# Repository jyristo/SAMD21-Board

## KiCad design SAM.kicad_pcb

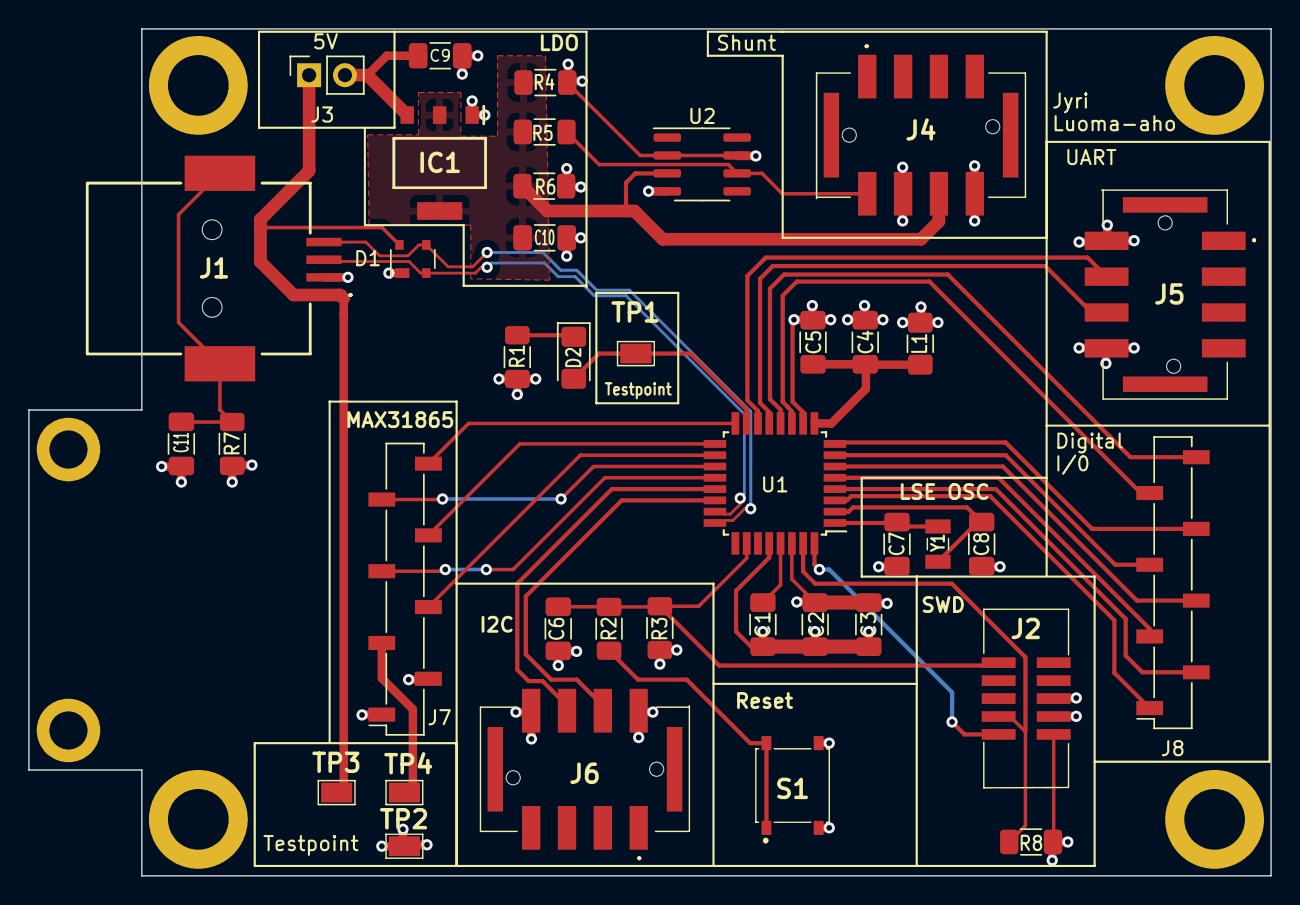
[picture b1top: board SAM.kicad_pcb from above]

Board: 4 copper layers, 88.0 x 60.0 mm, 45 parts (0 on the bottom side), 37 nets.

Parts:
C1, C6, C7, C8: 1uF; C_1206_3216Metric_Pad1.33x1.80mm_HandSolder
C2, C4, C9, C10: 10uF; C_1206_3216Metric_Pad1.33x1.80mm_HandSolder
C3, C5: 100nF; C_1206_3216Metric_Pad1.33x1.80mm_HandSolder
C11: 4.7nF; C_1206_3216Metric_Pad1.33x1.80mm_HandSolder
D1: PRTR5V0U2X; SOT-143
D2: LED; LED_1206_3216Metric_Pad1.42x1.75mm_HandSolder
H1, H2, H3, H4: M4 MountingHole; MountingHole_4.3mm_M4_ISO14580_Pad
H5, H6: M2.6 MountingHole; MountingHole_2.7mm_M2.5_ISO14580_Pad
IC1: NCV1117ST33T3G; SOT230P700X180-4N
J1: USB_B; KUSBXSMTBS1NB30
J2: 2002152100010E1LF
J3: SW_UIN; PinSocket_1x02_P2.54mm_Vertical
J4, J5, J6: 14010413101000
J7, J8: 2212SM-08G-75-B1-PCR; PinSocket_1x08_P2.54mm_Vertical_SMD_Pin1Right
L1: 30nH; L_1206_3216Metric_Pad1.42x1.75mm_HandSolder
R1: 820; R_1206_3216Metric_Pad1.30x1.75mm_HandSolder
R2: 330; R_1206_3216Metric_Pad1.30x1.75mm_HandSolder
R3: 2.2k; R_1206_3216Metric_Pad1.30x1.75mm_HandSolder
R4: 100m; R_1206_3216Metric_Pad1.30x1.75mm_HandSolder
R5: 100k; R_1206_3216Metric_Pad1.30x1.75mm_HandSolder
R6, R8: 1k; R_1206_3216Metric_Pad1.30x1.75mm_HandSolder
R7: 1M; R_1206_3216Metric_Pad1.30x1.75mm_HandSolder
S1: PTS526_SK15_SMTR2_LFS; PTS526SK15SMTR2LFS
TP1: LED; S275146R
TP2: GND; S275146R
TP3: VBUS; S275146R
TP4: 3.3V; S275146R
U1: ATSAMD21E18A-A; TQFP-32_7x7mm_P0.8mm
U2: MCP6L91RT-ESN; SOIC-8_3.9x4.9mm_P1.27mm
Y1: FC-135_32.7680KA-A5; FC135327680KAA5

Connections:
3V3_MAXOUT: J7.3, TP4.1
+3.3V: C2.2, C3.2, C6.2, J2.1 (VTref), J4.4, J5.2, J6.2, J7.1, L1.1, R3.2, R4.2, R8.1, U1.30 (VDDIN), U2.2 (-), U2.7 (V+)
+3.3VA: C4.2, C5.2, L1.2, U1.9 (VDDANA)
/LDO/SHUNT+: C10.1, IC1.2 (OUTPUT_1), IC1.4 (OUTPUT_2), J4.6, R4.1, R5.1, R6.2, U2.3 (+)
/LDO/SHUNTOUT: J4.2, R5.2, U2.6
/LDO/USB_VBUS: C9.1, IC1.3 (INPUT), J3.2
A0D14: J8.1, U1.3 (PA02)
A3D17: J8.3, U1.5 (PA04)
A4D18: J8.4, U1.6 (PA05)
AREF: J8.2, U1.4 (PA03)
D3: J8.8, U1.12 (PA09)
D4: J8.7, U1.11 (PA08)
D8: J8.5, U1.7 (PA06)
D9: J8.6, U1.8 (PA07)
DRDY: J7.8, U1.16 (PA15)
GND: C1.1, C2.1, C3.1, C4.1, C5.1, C7.1, C8.1, C9.2, C10.2, C11.2, D1.1 (GND), IC1.1 (GROUND), J1.4 (GND), J2.3 (GND), J2.5 (GND), J4.8, J5.8, J6.8, J7.2, R1.1, R6.1, R7.2, S1.3 (NO_1), S1.4 (NO_2), TP2.1, U1.10 (GND), U1.28 (GND), U2.4 (V-)
LED: D2.2 (A), TP1.1, U1.15 (PA14)
unnamed: D2.1 (K), R1.2
unnamed: R2.2, S1.1 (COM_1), S1.2 (COM_2)
unnamed: C1.2, U1.29 (VDDCORE)
RESET: C6.1, J2.10 (~RESET), R2.1, R3.1, U1.26 (~RESET)
SCL: J6.4, U1.22 (PA23)
SCLK: J7.4, U1.18 (PA17)
SDA: J6.6, U1.21 (PA22)
SDI: J7.6, U1.17 (PA16)
SDO: J7.5, U1.20 (PA19)
SHIELD: C11.1, J1.MP1, J1.MP2, R7.1
SWCLK: J2.4 (SWDCLK/TCK), R8.2, U1.31 (PA30)
SWDIO: J2.2 (SWDIO/TMS), U1.32 (PA31)
UART_RX: J5.4, U1.14 (PA11)
UART_TX: J5.6, U1.13 (PA10)
USB_D+: D1.3 (I/O2), J1.3 (D+), U1.24 (PA25)
USB_D-: D1.2 (I/O1), J1.2 (D-), U1.23 (PA24)
VBUS: D1.4 (VCC), J1.1 (VBUS), J3.1, TP3.1
XIN32: C7.2, U1.1 (PA00), Y1.1
XOUT32: C8.2, U1.2 (PA01), Y1.2
nCS: J7.7, U1.19 (PA18)

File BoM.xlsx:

Designator | Description | Footprint | Value | Manufacturer | Manufacturer Part Number | Vendor Link | Price | Quantity
Y1 | Crystals MINI SMD XTL 38.768 kHz | FC135327680KAA5 | FC-135_32.7680KA-A5 | Epson Timing | FC-135 32.7680KA-A5 | https://www.mouser.fi/ProductDetail/Epson-Timing/FC-135-32.7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 | 0.54 | 1
U2 | Instrumentation Amplifiers Sin, 500kHz, 800uA Gmin 1 v/v, I/O | SOIC-8_3.9x4.9mm_P1.27mm | MCP6L91RT-ESN | Microchip Technology | MCP6L91RT-ESN | https://www.mouser.fi/ProductDetail/Microchip-Technology/MCP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 | 1.58 | 1
U1 | ARM MCU 64KB 8KB32TQFP GRN 1.6-3.6V 48MHz | TQFP-32_7x7mm_P0.8mm | ATSAMD21E18A-AU | Microchip Technology | ATSAMD21E18A-AU | https://www.mouser.fi/ProductDetail/Microchip-Technology/ATS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 | 3.74 | 1
TP4 | Circuit Board Hardware - PCB SMT Mini Test Terminal, Reel | S275146R | 3.3V | Harwin | S2751-46R | https://www.mouser.fi/ProductDetail/Harwin/S2751-46R?qs=Daxo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 | 0.27900000000000003 | 1
TP3 | Circuit Board Hardware - PCB SMT Mini Test Terminal, Reel | S275146R | VBUS | Harwin | S2751-46R | https://www.mouser.fi/ProductDetail/Harwin/S2751-46R?qs=Daxo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 | 0.27900000000000003 | 1
TP2 | Circuit Board Hardware - PCB SMT Mini Test Terminal, Reel | S275146R | GND | Harwin | S2751-46R | https://www.mouser.fi/ProductDetail/Harwin/S2751-46R?qs=Daxo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 | 0.27900000000000003 | 1
TP1 | Circuit Board Hardware - PCB SMT Mini Test Terminal, Reel | S275146R | LED | Harwin | S2751-46R | https://www.mouser.fi/ProductDetail/Harwin/S2751-46R?qs=Daxo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 | 0.27900000000000003 | 1
S1 | Tactile Switches 50mA 12VDC | PTS526SK15SMTR2LFS | PTS526_SK15_SMTR2_LFS | C&K | PTS526_SK15_SMTR2_LFS | https://www.mouser.fi/ProductDetail/CK/PTS526-SK15-SMTR2-LFS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 | 0.108 | 1
R8,R6 | Thick Film Resistors - SMD 1K 1% | R_1206_3216Metric_Pad1.30x1.75mm_HandSolder | 1k | Bourns | CR1206-FX-1001ELF | https://www.mouser.fi/ProductDetail/Bourns/CR1206-FX-1001ELF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 | 0.09 | 2
R7 | Thick Film Resistors - SMD 1M 1% | R_1206_3216Metric_Pad1.30x1.75mm_HandSolder | 1M | Bourns | CR1206-FX-1004ELF | https://www.mouser.fi/ProductDetail/Bourns/CR1206-FX-1004ELF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 | 0.09 | 1
R5 | Thick Film Resistors - SMD 100K 1% | R_1206_3216Metric_Pad1.30x1.75mm_HandSolder | 100k | Bourns | CR1206-FX-1003ELF | https://www.mouser.fi/ProductDetail/Bourns/CR1206-FX-1003ELF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 | 0.09 | 1
R4 | Current Sense Resistors - SMD 0.1ohm 1% | R_1206_3216Metric_Pad1.30x1.75mm_HandSolder | 100m | Bourns | CRL1206-FW-R100ELF | https://www.mouser.fi/ProductDetail/Bourns/CRL1206-FW-R100EL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 | 0.19800000000000001 | 1
R3 | Thick Film Resistors - SMD 2.2K 1% | R_1206_3216Metric_Pad1.30x1.75mm_HandSolder | 2.2k | Bourns | CR1206-FX-2201ELF | https://www.mouser.fi/ProductDetail/Bourns/CR1206-FX-2201ELF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 | 0.09 | 1
R2 | Thick Film Resistors - SMD 330ohm 1% | R_1206_3216Metric_Pad1.30x1.75mm_HandSolder | 330 | Bourns | CR1206-FX-3300ELF | https://www.mouser.fi/ProductDetail/Bourns/CR1206-FX-3300ELF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 | 0.09 | 1
R1 | SMD Chip Resistor, 820 ohm, ± 0.1% | R_1206_3216Metric_Pad1.30x1.75mm_HandSolder | 820 | Panasonic | ERA8AEB821V | https://uk.farnell.com/panasonic/era8aeb821v/res-820r-0-1-0-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 | 0.20300000000000001 | 1
L1 | OPTIONAL LC FILTER FOR VDDANALOG | L_1206_3216Metric_Pad1.42x1.75mm_HandSolder | 30nH | - | - | - | - | -
J8,J7 | Board-to-Board, 2.54 mm, 1 Rows, 8 Contacts, Surface Mount | PinSocket_1x08_P2.54mm_Vertical_SMD_Pin1Right | 2212SM-08G-75-B1-PCR | MULTICOMP PRO | 2212SM-08G-75-B1-PCR | https://uk.farnell.com/multicomp/2212sm-08g-75-b1-pcr/connec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 | 0.59299999999999997 | 2
J6,J5,J4 | Fixed Terminal Blocks 4P 24-20 AWG spring MALE 12P | 14010413101000 | 14010413101000 | HARTING | 14010413101000 | https://www.mouser.fi/ProductDetail/HARTING/14010413101000?q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 | 1.52 | 3
J3 | Fixed Terminal Blocks 2P SIDE ENTRY 2.54mm | PinSocket_1x02_P2.54mm_Vertical | SW_UIN | TE Connectivity | 282834-2 | https://www.mouser.fi/ProductDetail/TE-Connectivity/282834-2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 | 1.8 | 1
J2 | 2002152100010E1LF | 2002152100010E1LF | 2002152100010E1LF | Amphenol | 20021521-00010E1LF | https://www.mouser.fi/ProductDetail/Amphenol-FCI/20021521-00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 | 1.75 | 1
J1 | USB Connectors B TYPE SMT RECPT BLACK 30u GOLD | KUSBXSMTBS1NB30 | USB_B | Kycon | KUSBX-SMT-BS1N-B30 | https://www.mouser.fi/ProductDetail/Kycon/KUSBX-SMT-BS1N-B30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 | 1.22 | 1
IC1 | LDO Voltage Regulators 3.3V 1.0A Automotive | SOT230P700X180-4N | NCV1117ST33T3G | onsemi | NCV1117ST33T3G | https://www.mouser.fi/ProductDetail/onsemi/NCV1117ST33T3G?qs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 | 0.60299999999999998 | 1
D2 | Standard LEDs - SMD WL-SMRW SMD RvMt Mon Watrclr Rect 1206Red | LED_1206_3216Metric_Pad1.42x1.75mm_HandSolder | LED | Wurth Elektronik | 156120RS75000 | https://www.mouser.fi/ProductDetail/Wurth-Elektronik/156120R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 | 0.18 | 1
D1 | ESD Suppressors / TVS Diodes PRTR5V0U2X/SOT143/SOT4 | SOT-143 | PRTR5V0U2X | Nexperia | PRTR5V0U2X,215 | https://www.mouser.fi/ProductDetail/Nexperia/PRTR5V0U2X215?q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 | 0.45 | 1
C8,C7,C6,C1 | Multilayer Ceramic Capacitors MLCC - SMD/SMT 50V 1uF X7R 1206 5% | C_1206_3216Metric_Pad1.33x1.80mm_HandSolder | 1uF | Samsung Electro-Mechanics | CL31B105KAHNNNE | https://www.mouser.fi/ProductDetail/Samsung-Electro-Mechanic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 | 0.11700000000000001 | 4
C5,C3 | Multilayer Ceramic Capacitors MLCC - SMD/SMT 50V 0.1uF X7R SMD 10% | C_1206_3216Metric_Pad1.33x1.80mm_HandSolder | 100nF | KEMET | C1206T104K5RACTU | https://www.mouser.fi/ProductDetail/KEMET/C1206T104K5RACTU?q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 | 0.84599999999999997 | 2
C11 | Multilayer Ceramic Capacitors MLCC - SMD/SMT 50V 4700pF X7R 1206 10% | C_1206_3216Metric_Pad1.33x1.80mm_HandSolder | 4.7nF | KEMET | C1206C472K5RAC | https://www.mouser.fi/ProductDetail/KEMET/C1206C472K5RAC?qs=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 | 0.108 | 1
C10,C9,C4,C2 | Multilayer Ceramic Capacitors MLCC - SMD/SMT 16V 10uF X7R 1206 10% | C_1206_3216Metric_Pad1.33x1.80mm_HandSolder | 10uF | Samsung Electro-Mechanics | CL31B106KAHNFNE | https://www.mouser.fi/ProductDetail/Samsung-Electro-Mechanic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 | 0.20699999999999999 | 4
 |  |  |  |  |  |  | Total Price | Total Quantity
 |  |  |  |  |  |  | 22.869999999999997 | 38
